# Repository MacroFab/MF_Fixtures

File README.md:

***
###MF_Fixtures
***
**Assembly Fixtures for MacroFab, INC.**

This repository contains files and information for assembly fixtures design by MacroFab, INC.

***
**License Information**

This project is under the [Creative Commons Attribution-ShareAlike 4.0 International License](LICENSE.md). These files are provided with no warranty and should be used at your own risk. 

***

| Directory | Description |
|---|---|
| FixtureOfFate | A fixture designed to hold MacroFab's 16"x16" prototype panels for Selective Solder. | 
| JigOfDestiny | A fixture designed to hold MacroFab's 16"x16" prototype panels. | 

***

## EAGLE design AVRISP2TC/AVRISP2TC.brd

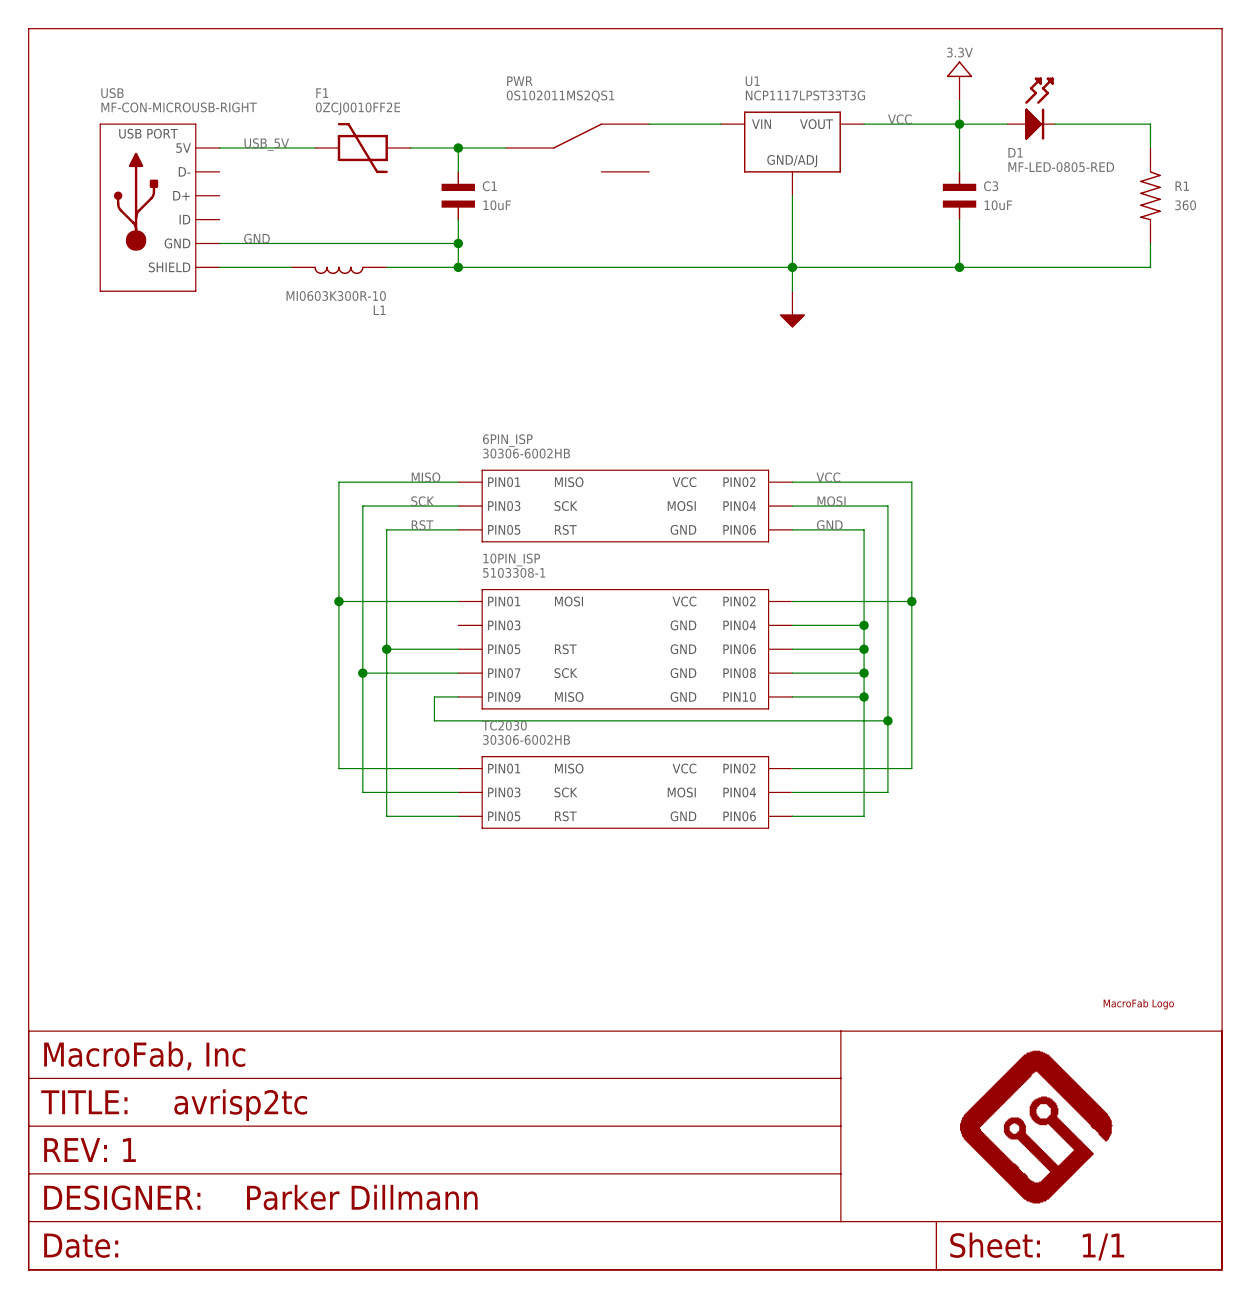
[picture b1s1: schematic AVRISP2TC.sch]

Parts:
6PIN_ISP: 30306-6002HB
10PIN_ISP: 5103308-1
C1, C3: 10uF; C1206; MPN MF-CAP-1206-10uF
D1: MF-LED-0805-RED; LED0805
F1: 0ZCJ0010FF2E; 1206; MPN 0ZCJ0010FF2E
FRAME1: MF_FRAMEDEFAULT; MF_FRAME_DEFAULT
L1: MI0603K300R-10; L0603; MPN MI0603K300R-10
PWR: 0S102011MS2QS1; MPN 0S102011MS2QS1
R1: 360; R0805; MPN MF-RES-0805-360
TC2030: 30306-6002HB
U1: NCP1117LPST33T3G; SOT-223-3
U$3: MF_LOGOLOGO_MEDIUM; MF_LOGO_MEDIUM
USB: MF-CON-MICROUSB-RIGHT; MICROUSB-RIGHT

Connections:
GND: 6PIN_ISP.6 (PIN6), 10PIN_ISP.4 (PIN4), 10PIN_ISP.6 (PIN6), 10PIN_ISP.8 (PIN8), 10PIN_ISP.10 (PIN10), C1.P$2, C3.P$2, L1.P$1, R1.P$2, TC2030.6 (PIN6), U1.P$2 (GND/ADJ), USB.5 (GND)
MISO: 6PIN_ISP.1 (PIN1), 10PIN_ISP.1 (PIN1), TC2030.1 (PIN1)
MOSI: 6PIN_ISP.4 (PIN4), 10PIN_ISP.9 (PIN9), TC2030.4 (PIN4)
unnamed: D1.CATHODE, R1.P$1
unnamed: C1.P$1, F1.2, PWR.2 (C)
unnamed: L1.P$2, USB.S1 (SLD), USB.S2 (SLD), USB.S3 (SLD), USB.S4 (SLD), USB.S5 (SLD), USB.S6 (SLD)
unnamed: PWR.1, U1.P$4 (VIN)
RST: 6PIN_ISP.5 (PIN5), 10PIN_ISP.5 (PIN5), TC2030.5 (PIN5)
SCK: 6PIN_ISP.3 (PIN3), 10PIN_ISP.7 (PIN7), TC2030.3 (PIN3)
USB_5V: F1.1, USB.1 (5V)
VCC: 6PIN_ISP.2 (PIN2), 10PIN_ISP.2 (PIN2), C3.P$1, D1.ANODE, TC2030.2 (PIN2), U1.P$1 (VOUT), U1.P$3 (VOUT)

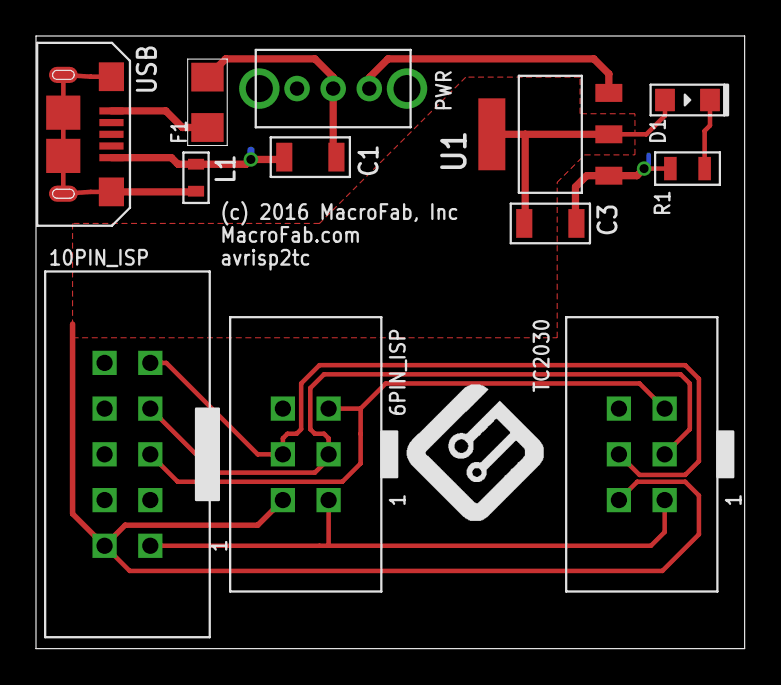
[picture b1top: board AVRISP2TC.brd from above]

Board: 2 copper layers, 39.4 x 34.0 mm, 14 parts (0 on the bottom side), 11 nets.

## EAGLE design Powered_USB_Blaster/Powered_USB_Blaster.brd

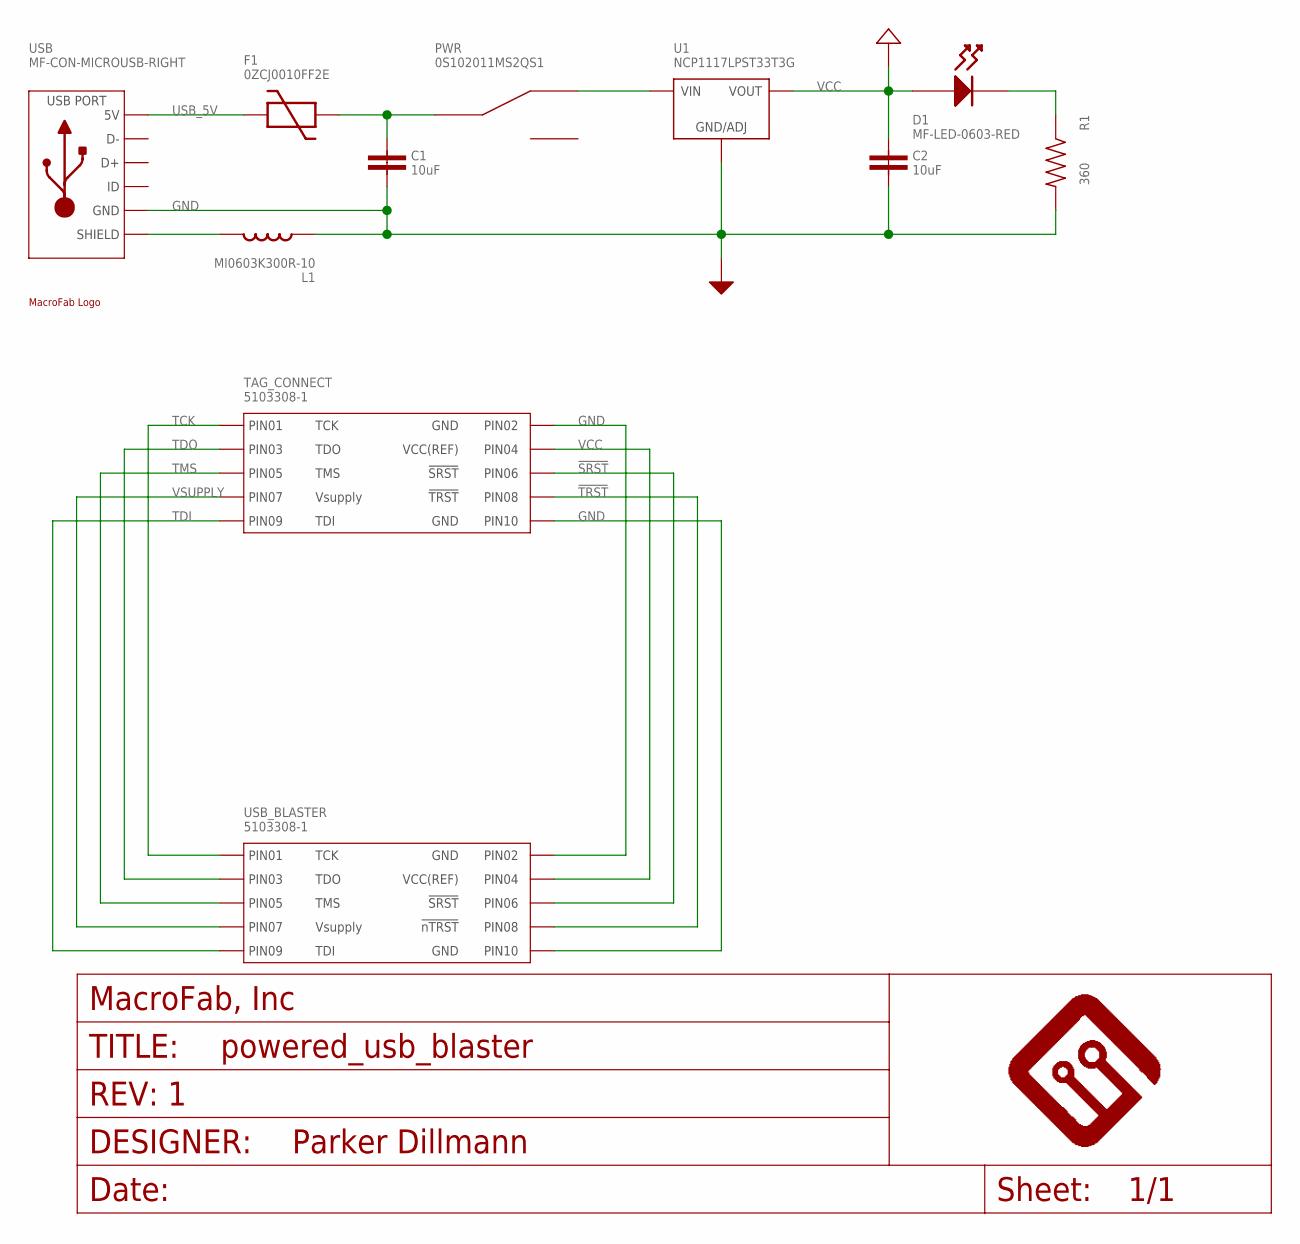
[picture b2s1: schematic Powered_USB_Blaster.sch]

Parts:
C1, C2: 10uF; 1206
D1: MF-LED-0603-RED; LED0805
F1: 0ZCJ0010FF2E; 1206
FRAME1: MF_FRAMEDEFAULT; MF_FRAME_DEFAULT
L1: MI0603K300R-10; L0603
PWR: 0S102011MS2QS1
R1: 360; R0805
TAG_CONNECT: 5103308-1
U1: NCP1117LPST33T3G; SOT-223-3
U$3: MF_LOGOLOGO_MEDIUM; MF_LOGO_MEDIUM
USB: MF-CON-MICROUSB-RIGHT; MICROUSB-RIGHT
USB_BLASTER: 5103308-1

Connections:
!SRST: TAG_CONNECT.6 (PIN6), USB_BLASTER.6 (PIN6)
!TRST: TAG_CONNECT.8 (PIN8), USB_BLASTER.8 (PIN8)
GND: C1.2, C2.2, L1.P$1, R1.P$2, TAG_CONNECT.2 (PIN2), TAG_CONNECT.10 (PIN10), U1.P$2 (GND/ADJ), USB.5 (GND), USB_BLASTER.2 (PIN2), USB_BLASTER.10 (PIN10)
unnamed: D1.CATHODE, R1.P$1
unnamed: C1.1, F1.2, PWR.2 (C)
unnamed: L1.P$2, USB.S1 (SLD), USB.S2 (SLD), USB.S3 (SLD), USB.S4 (SLD), USB.S5 (SLD), USB.S6 (SLD)
unnamed: PWR.1, U1.P$4 (VIN)
TCK: TAG_CONNECT.1 (PIN1), USB_BLASTER.1 (PIN1)
TDI: TAG_CONNECT.9 (PIN9), USB_BLASTER.9 (PIN9)
TDO: TAG_CONNECT.3 (PIN3), USB_BLASTER.3 (PIN3)
TMS: TAG_CONNECT.5 (PIN5), USB_BLASTER.5 (PIN5)
USB_5V: F1.1, USB.1 (5V)
VCC: C2.1, D1.ANODE, TAG_CONNECT.4 (PIN4), U1.P$1 (VOUT), U1.P$3 (VOUT), USB_BLASTER.4 (PIN4)
VSUPPLY: TAG_CONNECT.7 (PIN7), USB_BLASTER.7 (PIN7)

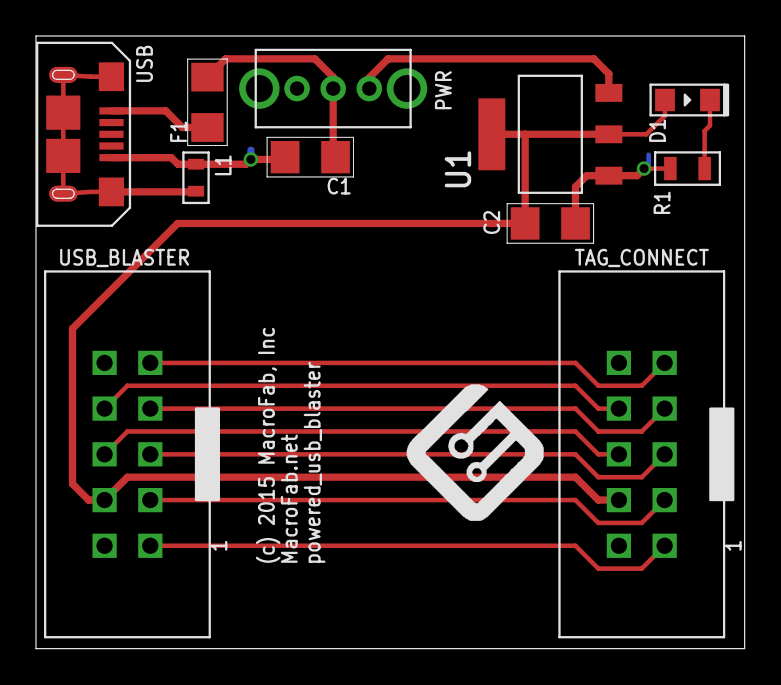
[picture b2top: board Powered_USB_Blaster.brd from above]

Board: 2 copper layers, 39.4 x 34.0 mm, 13 parts (0 on the bottom side), 14 nets.

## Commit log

2016-06-01 Added Powered USB Blaster
2016-06-13 First push of the JoD
2016-06-13 Modded the Fixture to be smaller
2016-07-19 Pushing SiLabs2TC
2016-07-25 V3 complete. 3D Files are in AutoDesk cloud.
2016-08-10 Added AVRISP2TC
2016-08-10 Pushing Camfiles
2016-08-10 Moving interconnect boards to Macro_Articles.
2016-08-10 Updating Jig of Destiny.
2016-08-18 FoF Push
2016-10-06 AJOD complete.

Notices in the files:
parts and their libraries:
MF_Aesthetics: (c) 2016 MacroFab, Inc
MF_Aesthetics: (c) 2015 MacroFab, Inc
